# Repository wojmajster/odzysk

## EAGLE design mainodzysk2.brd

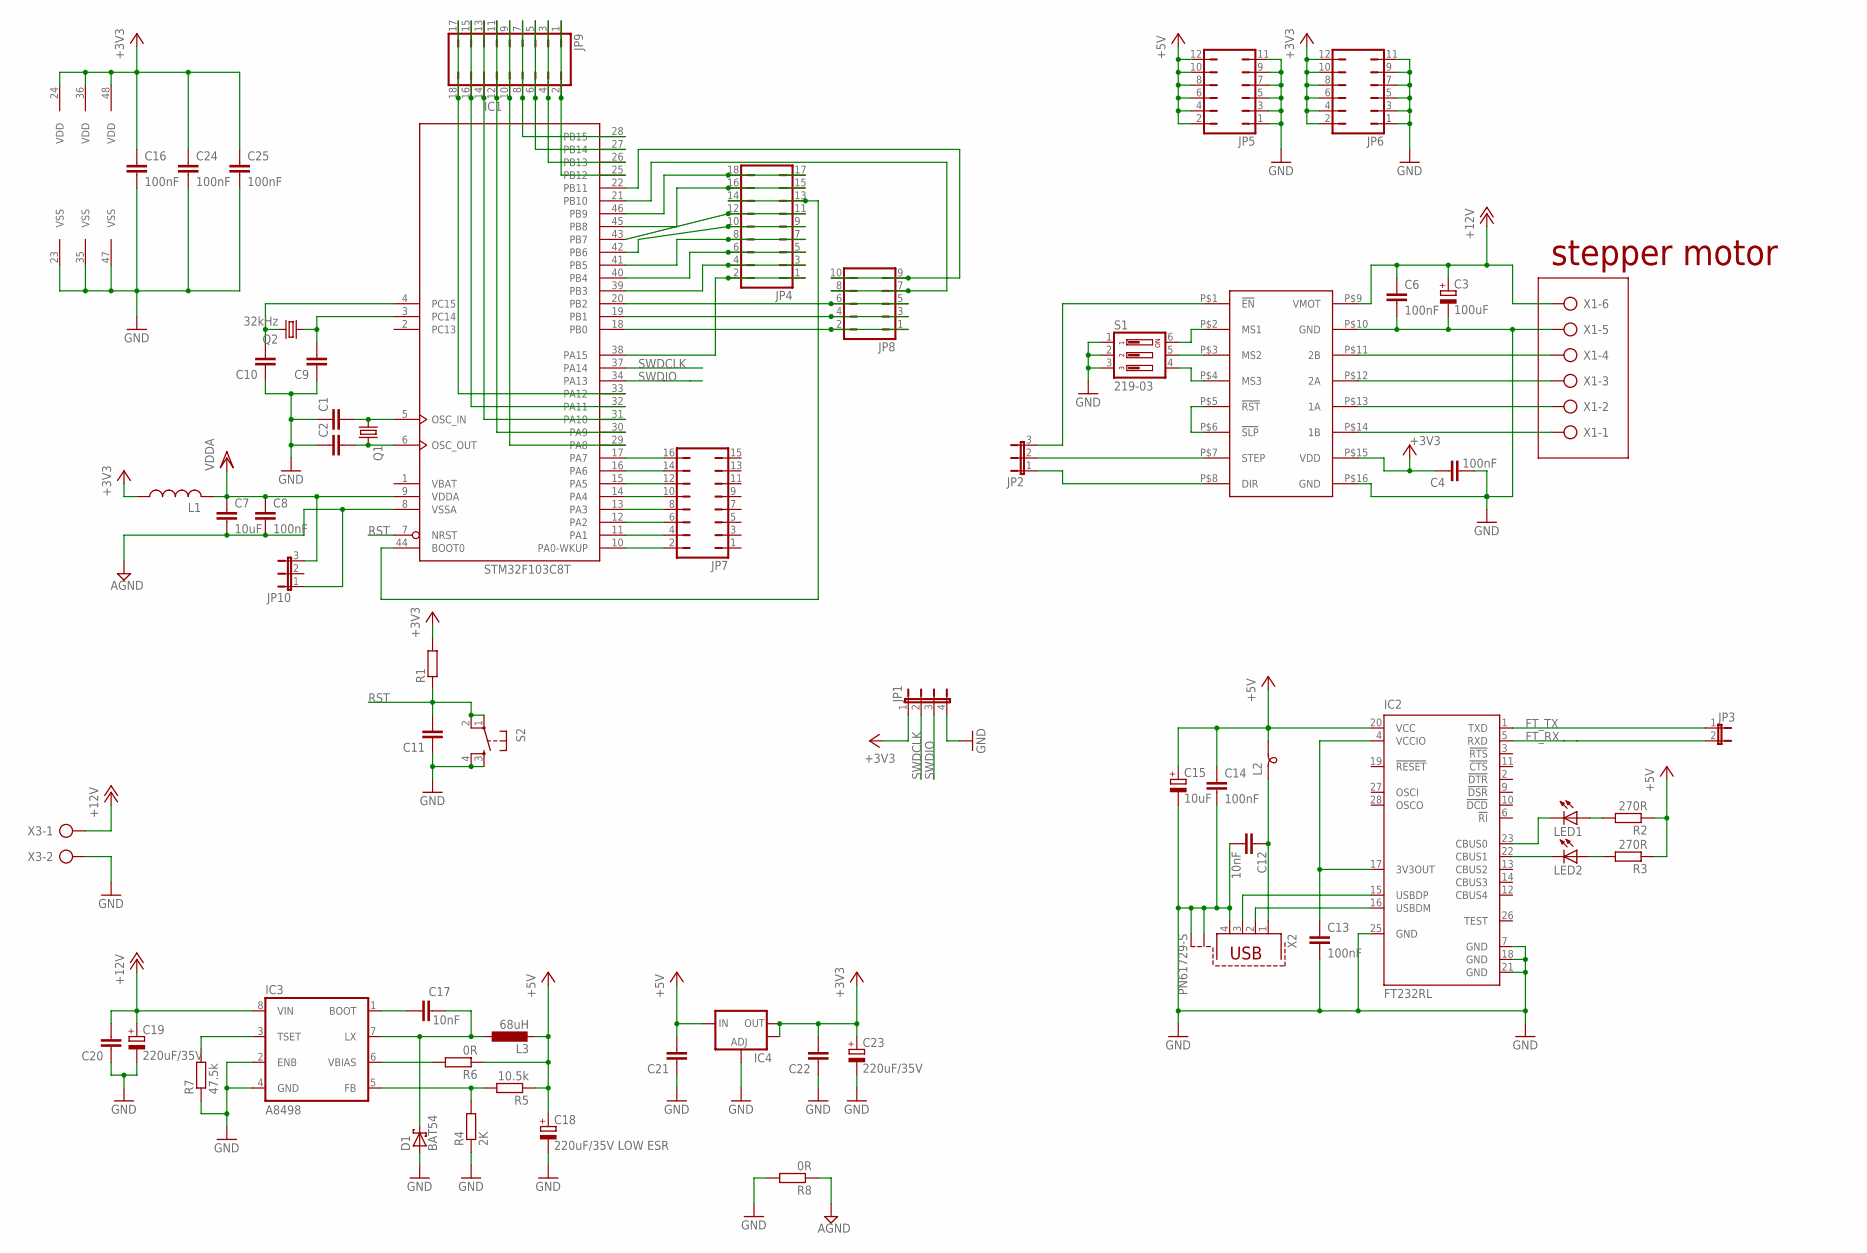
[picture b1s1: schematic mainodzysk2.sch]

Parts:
C1, C2, C9, C10, C11, C20, C21, C22: C-EUC0603K; C0603K
C3: 100uF; E5-10,5
C4, C6, C8, C13, C14, C24: 100nF; C0603K
C7: 10uF; C1812
C12: 10nF; C0603K
C15: 10uF; E5-10,5
C16: 100nF; C025-025X050
C17: 10nF; C050-030X075
C18: 220uF/35V LOW ESR; E5-10,5
C19, C23: 220uF/35V; E5-10,5
C25: 100nF; C025-024X044
D1: BAT54; SOT23
IC1: STM32F103C8T; LQFP48
IC2: FT232RL; SSOP28
IC3: A8498; SO08
IC4: V_REG_LM1117SOT223; SOT223
JP1: JP4E; JP4
JP2: JP2E; JP2
JP3: JP1E; JP1
JP4, JP9: JP9Q
JP5, JP6: JP6Q
JP7: JP8Q
JP8: JP5Q
JP10: JP2W
L1: L-USL2012C; L2012C
L2: SM-B5
L3: 68uH; PIS2816
LED1, LED2: LEDCHIPLED_0805; CHIPLED_0805
Q1: CRYSTALHC49UP; HC49UP
Q2: 32kHz; TC26H
R1: R-EU_R0805; R0805
R2, R3: 270R; R0805
R4: 2K; 0207/12
R5: 10.5k; R0805
R6: 0R; R0805
R7: 47.5k; R0805
R8: 0R; 0207/10
S1: 219-03; CTS-219-03
S2: TAC_SWITCHPTH; TACTILE-PTH
U$1: A4988_POLOLU_STEPER_MOTOR; 6X8
X1: AK300/6
X2: PN61729-S
X3: AK300/2

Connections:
+3V3: C4.1, C16.1, C22.2, C23.+, C24.1, C25.1, IC1.24 (VDD), IC1.36 (VDD), IC1.48 (VDD), IC4.2 (OUT), IC4.4 (OUT), JP1.1, JP6.2, JP6.4, JP6.6, JP6.8, JP6.10, JP6.12, L1.1, R1.2, U$1.P$15 (VDD)
+5V: C14.1, C15.+, C18.+, C21.2, IC2.20 (VCC), IC4.3 (IN), JP5.2, JP5.4, JP5.6, JP5.8, JP5.10, JP5.12, L2.2, L3.2, R2.1, R3.1, R5.1, R6.1
+12V: C3.+, C6.1, C19.+, C20.2, IC3.8 (VIN), U$1.P$9 (VMOT), X1.6, X3.1
AGND: C7.2, C8.2, IC1.8 (VSSA), JP10.1, R8.1
FT_RX: IC2.5 (RXD), JP3.2
FT_TX: IC2.1 (TXD), JP3.1
GND: C1.1, C2.1, C3.-, C4.2, C6.2, C9.1, C10.1, C11.1, C12.2, C13.2, C14.2, C15.-, C16.2, C18.-, C19.-, C20.1, C21.1, C22.1, C23.-, C24.2, C25.2, D1.1 (A), IC1.23 (VSS), IC1.35 (VSS), IC1.47 (VSS), IC2.7 (GND), IC2.18 (GND), IC2.21 (GND), IC2.25 (GND), IC3.2 (ENB), IC3.4 (GND), IC4.1 (ADJ), JP1.4, JP5.1, JP5.3, JP5.5, JP5.7, JP5.9, JP5.11, JP6.1, JP6.3, JP6.5, JP6.7, JP6.9, JP6.11, R4.1, R7.1, R8.2, S1.1, S1.2, S1.3, S2.3, S2.4, U$1.P$10 (GND), U$1.P$16 (GND), X1.5, X2.4, X2.S1, X2.S2, X3.2
unnamed: C1.2, IC1.5 (OSC_IN), Q1.1
unnamed: C2.2, IC1.6 (OSC_OUT), Q1.2
unnamed: U$1.P$5 (!RST), U$1.P$6 (!SLP)
unnamed: C10.2, IC1.4 (PC15), Q2.2
unnamed: U$1.P$14 (1B), X1.1
unnamed: U$1.P$13 (1A), X1.2
unnamed: U$1.P$12 (2A), X1.3
unnamed: S1.6, U$1.P$2 (MS1)
unnamed: U$1.P$11 (2B), X1.4
unnamed: S1.5, U$1.P$3 (MS2)
unnamed: S1.4, U$1.P$4 (MS3)
unnamed: C9.2, IC1.3 (PC14), Q2.1
unnamed: IC2.15 (USBDP), X2.3
unnamed: IC2.16 (USBDM), X2.2
unnamed: C12.1, L2.1, X2.1
unnamed: IC3.6 (VBIAS), R6.2
unnamed: C13.1, IC2.4 (VCCIO), IC2.17 (3V3OUT)
unnamed: IC3.3 (TSET), R7.2
unnamed: IC3.5 (FB), R4.2, R5.2
unnamed: IC2.23 (CBUS0), LED1.C
unnamed: IC2.22 (CBUS1), LED2.C
unnamed: LED1.A, R2.2
unnamed: LED2.A, R3.2
unnamed: IC1.46 (PB9), JP4.17, JP4.18
unnamed: JP2.3, U$1.P$1 (!EN)
unnamed: C17.2, IC3.1 (BOOT)
unnamed: C17.1, D1.3 (C), IC3.7 (LX), L3.1
unnamed: JP2.2, U$1.P$7 (STEP)
unnamed: JP2.1, U$1.P$8 (DIR)
unnamed: IC1.45 (PB8), JP4.15, JP4.16
unnamed: IC1.10 (PA0-WKUP), JP7.2
unnamed: IC1.43 (PB7), JP4.11, JP4.12
unnamed: IC1.42 (PB6), JP4.9, JP4.10
unnamed: IC1.41 (PB5), JP4.7, JP4.8
unnamed: IC1.40 (PB4), JP4.5, JP4.6
unnamed: IC1.44 (BOOT0), JP4.13, JP4.14
unnamed: IC1.38 (PA15), JP4.1, JP4.2
unnamed: IC1.39 (PB3), JP4.3, JP4.4
unnamed: IC1.11 (PA1), JP7.4
unnamed: IC1.12 (PA2), JP7.6
unnamed: IC1.13 (PA3), JP7.8
unnamed: IC1.14 (PA4), JP7.10
unnamed: IC1.15 (PA5), JP7.12
unnamed: IC1.16 (PA6), JP7.14
unnamed: IC1.17 (PA7), JP7.16
unnamed: IC1.18 (PB0), JP8.1, JP8.2
unnamed: IC1.19 (PB1), JP8.3, JP8.4
unnamed: IC1.20 (PB2), JP8.5, JP8.6
unnamed: IC1.22 (PB11), JP8.9, JP8.10
unnamed: IC1.21 (PB10), JP8.7, JP8.8
unnamed: IC1.25 (PB12), JP9.1, JP9.2
unnamed: IC1.26 (PB13), JP9.3, JP9.4
unnamed: IC1.27 (PB14), JP9.5, JP9.6
unnamed: IC1.28 (PB15), JP9.7, JP9.8
unnamed: IC1.29 (PA8), JP9.9, JP9.10
unnamed: IC1.30 (PA9), JP9.11, JP9.12
unnamed: IC1.31 (PA10), JP9.13, JP9.14
unnamed: IC1.32 (PA11), JP9.15, JP9.16
unnamed: IC1.33 (PA12), JP9.17, JP9.18
RST: C11.2, IC1.7 (NRST), R1.1, S2.1, S2.2
SWDCLK: IC1.37 (PA14), JP1.2
SWDIO: IC1.34 (PA13), JP1.3
VBAT: IC1.1 (VBAT)
VDD: C7.1, C8.1, IC1.9 (VDDA), JP10.3, L1.2

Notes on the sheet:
stepper motor

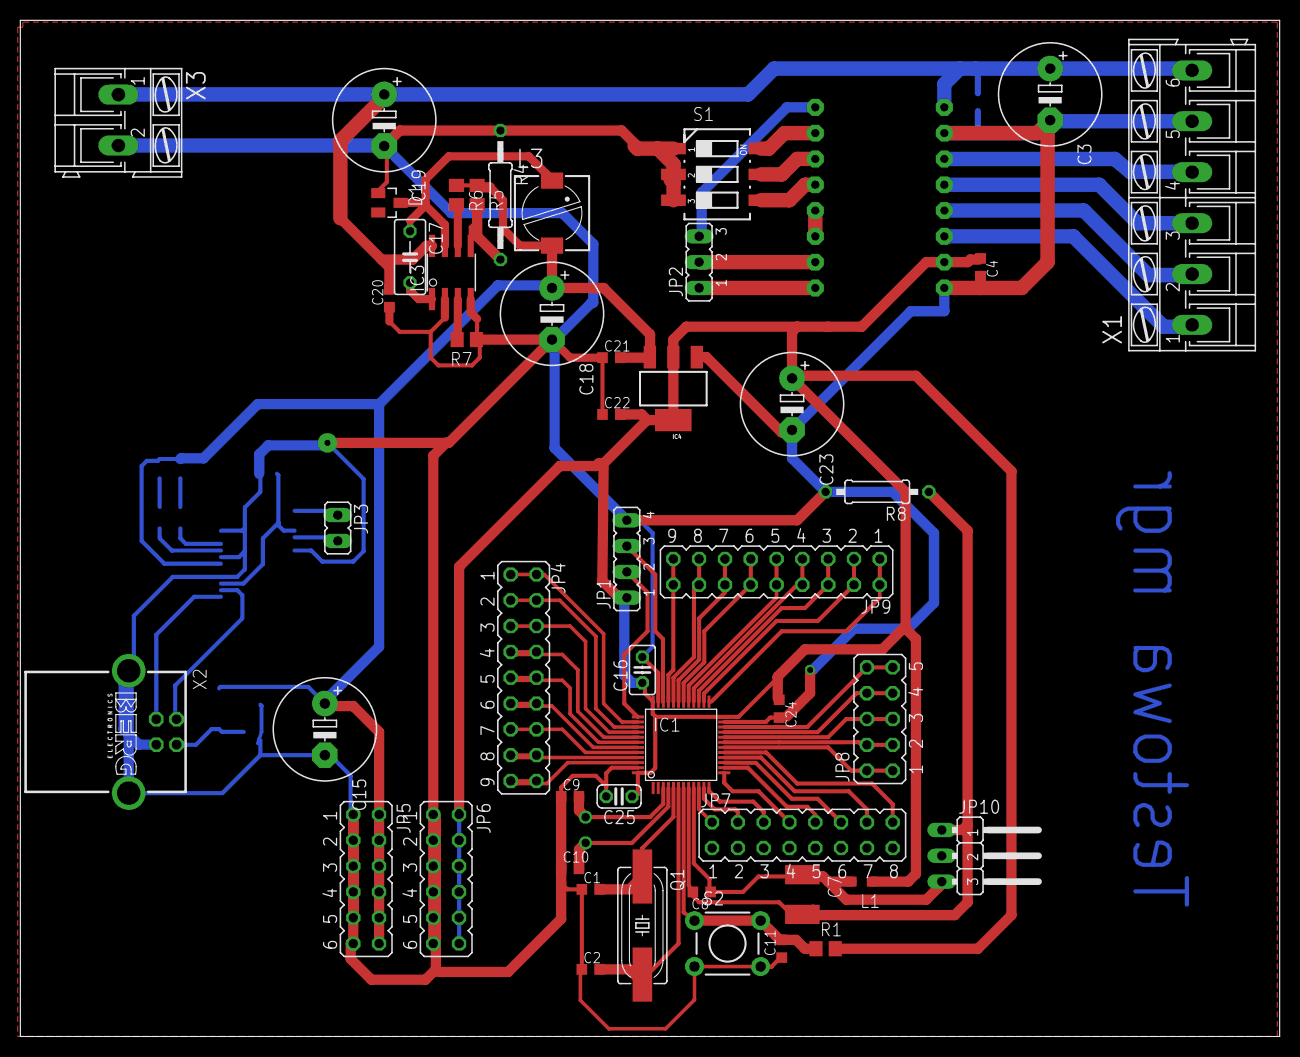
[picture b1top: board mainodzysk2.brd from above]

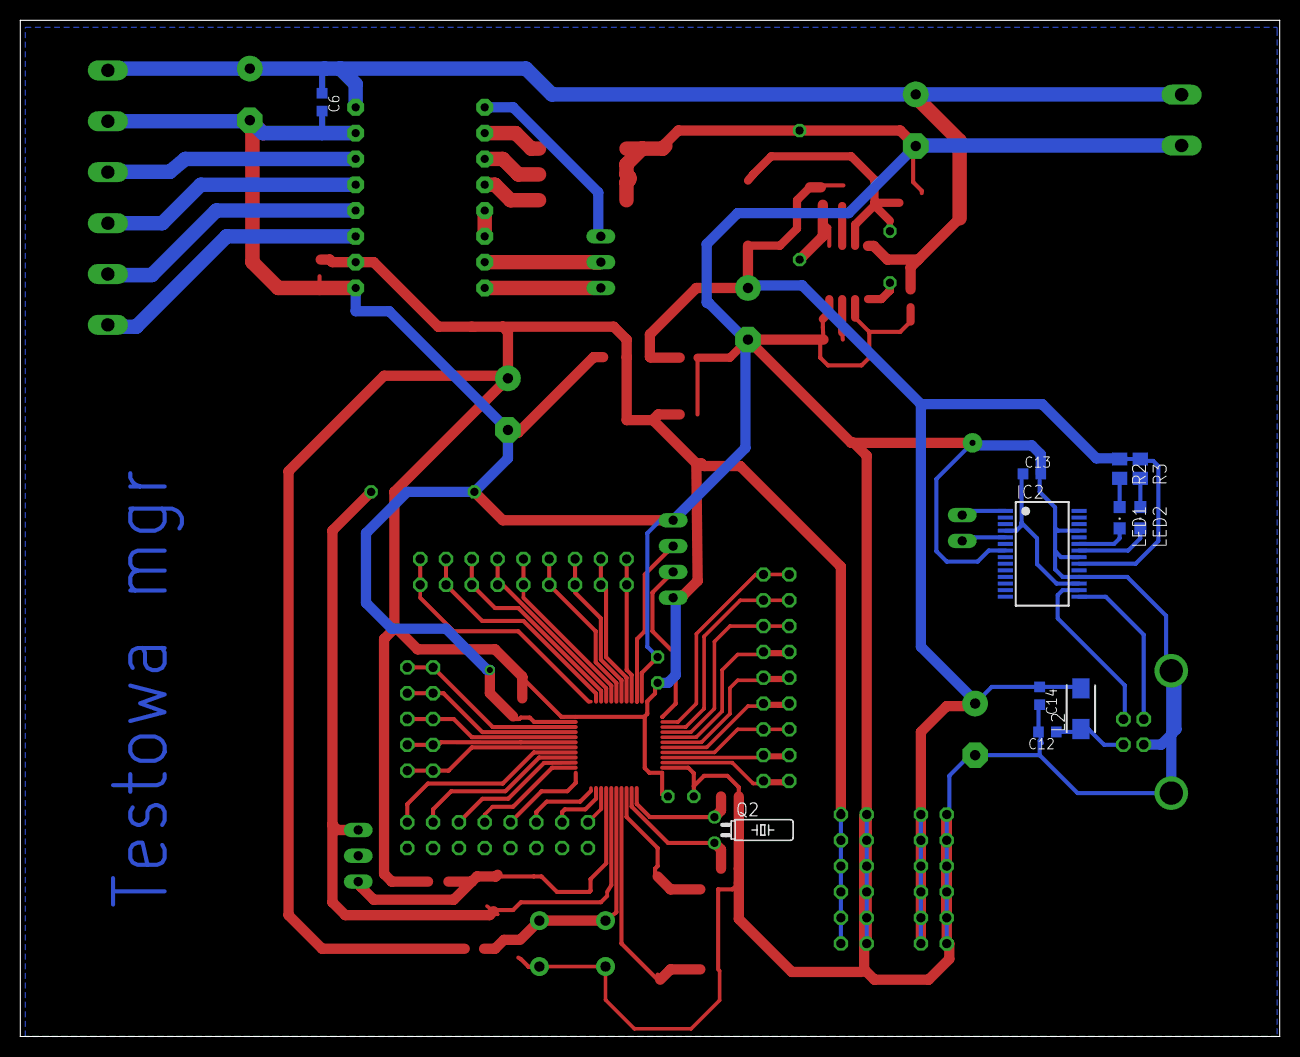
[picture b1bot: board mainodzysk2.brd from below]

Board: 2 copper layers, 123.9 x 100.0 mm, 60 parts (11 on the bottom side), 70 nets.

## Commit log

2015-09-03 :circus_tent: Added .gitattributes & .gitignore files
2015-09-03 Testowe_pcb_magisterka
    wykonano PCB 29.08.2015

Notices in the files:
parts and their libraries:
SparkFun: Licensing: CC v3.0 Share-Alike You are welcome to use this library for commercial purposes.
